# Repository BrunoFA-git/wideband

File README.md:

# gerEFI Wideband Controller

[User Documentation](https://gerefi.com/s/wb)

## Building Firmware

The `firmware/boards` directory contains configuration for each board this firmware supports.

For the standalone board and the module built in to gerEFI Hellen boards, `f0_module` is the correct target.  Use the `build_wideband.sh` script to build and package the wideband firmware: both a bin including the bootloader, and a header file consumed by gerEFI that contains no bootloader, to be uploaded over CAN (via the aforementioned bootloader).

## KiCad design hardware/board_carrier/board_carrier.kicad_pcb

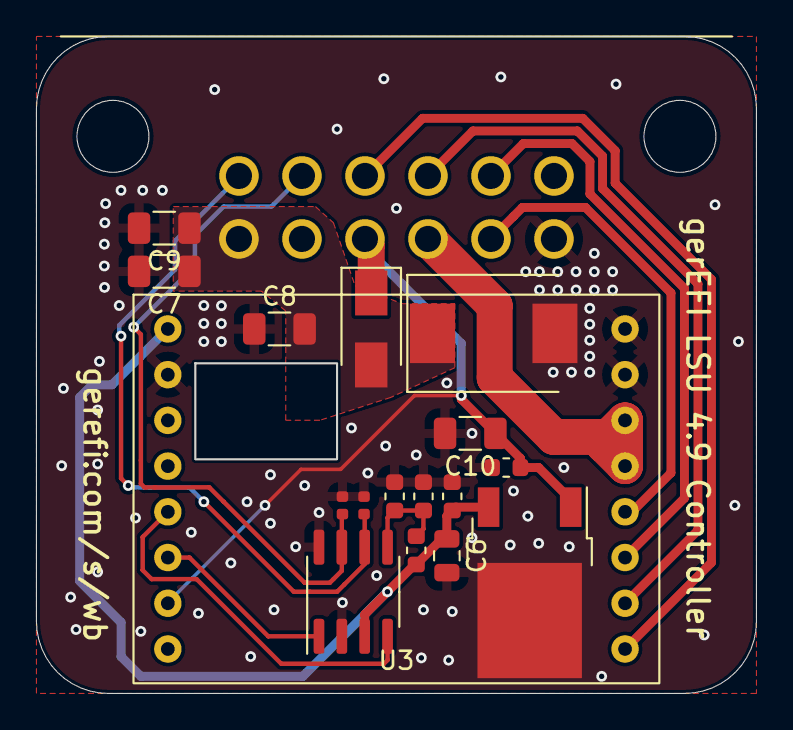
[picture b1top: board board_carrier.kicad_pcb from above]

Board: 2 copper layers, 39.9 x 36.4 mm, 18 parts (0 on the bottom side), 14 nets.

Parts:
C1, C2, C3: 1u; C_0603_1608Metric
C4, C5: 47p; C_0402_1005Metric
C6: 22u; C_0805_2012Metric
C7, C8, C9, C10: 10u; C_1206_3216Metric
D1: D_TVS; D_SMC
D2: D_Schottky; D_SMA
J3: Conn_02x06_Top_Bottom; mx120g-12
R1: 220; R_0603_1608Metric
R2: 470; R_0603_1608Metric
U1: TJA1051T-3; SOIC-8_3.9x4.9mm_P1.27mm
U2: LM78M05_TO252; TO-252-2
U3: f042_wideband_module

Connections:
12V_RAW: C7.1, C8.2, C9.1, D1.1 (A1), D2.2 (A), J3.6
+5V: C2.1, C6.1, R1.1, U1.3 (VCC), U2.3 (VO), U3.1 (5V)
/CAN_H: C4.2, J3.11, U1.7 (CANH)
/CAN_L: C5.1, J3.12, U1.6 (CANL)
/CAN_RX: U1.4 (RXD), U3.5 (CAN_RX)
/CAN_TX: U1.1 (TXD), U3.6 (CAN_TX)
/LSU_Heater+: C1.1, C10.1, D2.1 (K), J3.4, U2.1 (VI), U3.7 (VBatt_Sense)
/LSU_Heater-: J3.3, U3.11 (HEATER-), U3.12 (HEATER-)
/LSU_Ip: J3.2, U3.13 (LSU_ip)
/LSU_Rtrim: J3.9, U3.15 (LSU_rtrim)
/LSU_Un: J3.10, U3.16 (LSU_un)
/LSU_Vm: J3.8, U3.14 (LSU_vm)
GND: C1.2, C2.2, C3.2, C4.1, C5.2, C6.2, C7.2, C8.1, C9.2, C10.2, D1.2 (A2), J3.1, R2.2, U1.2 (GND), U1.8 (S), U2.2 (GND), U3.2 (GND), U3.9 (HEAT_GND), U3.10 (HEAT_GND2)
unnamed: C3.1, R1.2, R2.1, U1.5 (VIO)

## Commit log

2025-05-26 add submodule
2025-05-26 add submodules
